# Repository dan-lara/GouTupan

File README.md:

# GouTupan

# User Guide —— GouTupan  

**Daniel, Vladislav, Xiaochen, Yulin**  

---

## Device Overview  

The system is an integrated environmental monitoring platform for agricultural greenhouses, based on an Arduino MKR WAN 1310 development board.  
Equipped with multiple specialized sensors, it enables real-time measurement of critical parameters for plant growth.  

Key features include:  
- Self-powered via solar panel with energy management circuit;  
- Waterproof design suitable for greenhouse environments with frequent irrigation;  
- Wireless data transmission via LoRaWAN;  
- Modular architecture for customized measurement points;  
- User interface: Web platform and local e-ink display for remote or on-site monitoring.  

---

## Installation and Usage Instructions  

The device transmits data using the LoRa protocol. Ensure the installation site has stable coverage from a LoRaWAN gateway.  
Without this, the following features will be unavailable: remote monitoring and historical data access.  

The system comprises four main modules:  
- **MCU Enclosure**: Contains the microcontroller and processing unit;  
- **"Mushroom" Sensor**: Measures ambient conditions;  
- **Soil Temperature & Humidity Sensor Array**;  
- **Solar Panel**: Powers the system.  

### MCU Enclosure  
Integrates an MKR WAN 1310 board, power management circuit, light sensor, and e-ink display.  
**Installation**: Position in a non-floodable area with direct ambient light exposure.  

### "Mushroom" Sensor  
Combines temperature, humidity, and gas sensors. Deploy at target measurement points.  
**Caution**: Avoid watering from below to prevent water ingress.  

### Soil Sensors  
- **Compact Probe**: Surface measurement (10 cm depth);  
- **Long Cylindrical Probe**: 50 cm length for deep soil measurements.  

### Solar Panel  
**Installation**: Place in a sunlit, elevated location to avoid water accumulation.  

### Activation  
Toggle the **side switch** on the MCU enclosure. Data transmission occurs every **3 minutes** (preconfigured).  

---

## Network and HMI Information  

### TTN (The Things Network)  
- **Username**: Levovitch  
- **Password**: demo1234  
- **Application Name**: `goutupan-mkr1310-vlad-xioa-dani-yuli`  
- **Device ID**: `goutupan-mkr1310-vlad-xioa-dani-yuli`  
- **AppEUI**: `AA2025AAAA2025AA`  
- **DevEUI**: `A8610A3234268310`  
- **AppKey**: `9qyh4jN6RBh4F@\$`  

### Useful Links  
- [Data Visualization Dashboard](https://goutupan.grafana.net/public-dashboards/d0bf3f14221d4401bc8c1fea2e30d045?var-device_var=goutupan-mkr1310-yulin-4&theme=light&from=now-7d&to=now&timezone=browser)  
- [Project GitHub Repository](https://github.com/dan-lara/GouTupan)  

---

## Sensor Specifications  

**Table 1: Technical Specifications of Environmental Sensors**  

| Module                     | Measured Parameters                                                                 | Technical Specifications                                                                 |
|----------------------------|-------------------------------------------------------------------------------------|------------------------------------------------------------------------------------------|
| **SCD30**                  | Carbon Dioxide (CO₂),<br>Temperature,<br>Humidity                                   | 400 ppm – 10,000 ppm (±30 ppm ±3%),<br>0–50 °C (±0.4 °C),<br>0–100% RH (±3% RH)         |
| **TCS34725/SI1145**        | Spectral Components (RGB/UV/IR)                                                    | λ = 465, 525, 615 nm,<br>Range: 400–1000 nm,<br>UV Detection: 280–400 nm (algorithmic)  |
| **SEN0605**                | Nitrogen (N), Phosphorus (P), Potassium (K)                                        | Range: 0–2999 mg/kg,<br>Resolution: 1 mg/kg,<br>Accuracy ≤5%,<br>IP68                   |
| **Grove Barometer 101020068** | Barometric Pressure                                                             | 30–110 kPa (±0.01 hPa)                                                                 |
| **SEN0322**                | Oxygen (O₂) Concentration                                                          | 0–25% vol (drift < 2%/month)                                                          |
| **SGP40**                  | Volatile Organic Compounds (VOC)                                                   | VOC Index: 0–500,<br>Ethanol: 0–1000 ppm                                              |
| **SHT30/SHT20**            | Temperature & Humidity                                                             | Humidity: 0–100% RH (±2%RH/±3%RH),<br>Temperature: -40–125 °C (±0.2 °C/±0.3 °C)       |
| **Grove Gas Sensor 101020820** | Ammonia (NH₃), <br>Carbon Monoxide (CO), <br>Nitrogen Dioxide (NO₂),<br>Propane (C₃H₈), <br>Butane (C₄H₁₀), <br>Methane (CH₄), <br>Hydrogen (H₂), <br>Ethanol (C₂H₅OH) | NH₃: 1–500 ppm,<br>CO: 5–5000 ppm,<br>NO₂: 0.05–2 ppm,<br>Hydrocarbons: 500–10,000 ppm,<br>H₂: 1–1000 ppm,<br>Ethanol: 1–500 ppm |

---

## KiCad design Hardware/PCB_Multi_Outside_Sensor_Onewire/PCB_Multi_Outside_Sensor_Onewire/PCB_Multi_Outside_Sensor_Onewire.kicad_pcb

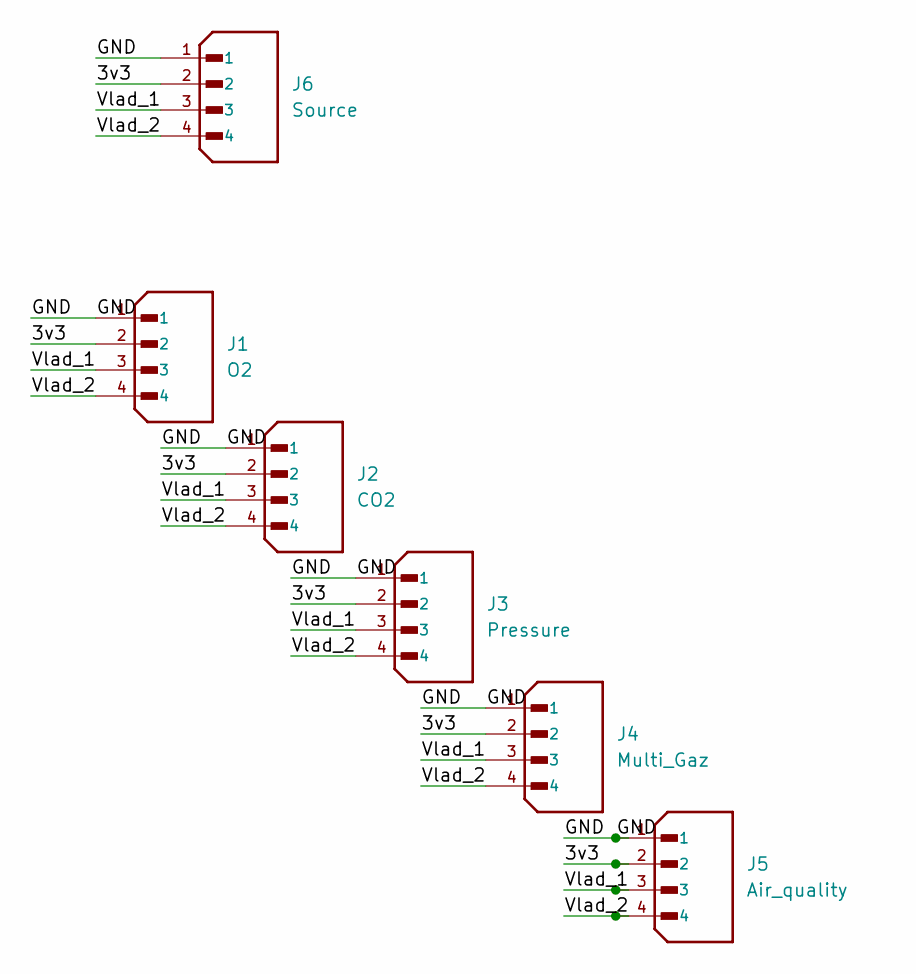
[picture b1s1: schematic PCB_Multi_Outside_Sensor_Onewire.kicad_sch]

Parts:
J1: O2; PinHeader_1x04_P2.00mm_Vertical; PARTREV 7/4/21
J2: CO2; PinHeader_1x04_P2.00mm_Vertical; PARTREV 7/4/21
J3: Pressure; PinHeader_1x04_P2.00mm_Vertical; PARTREV 7/4/21
J4: Multi_Gaz; PinHeader_1x04_P2.00mm_Vertical; PARTREV 7/4/21
J5: Air_quality; PinHeader_1x04_P2.00mm_Vertical; PARTREV 7/4/21
J6: Source; PinHeader_1x04_P2.00mm_Vertical; PARTREV 7/4/21

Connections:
/3v3: J1.2, J2.2, J3.2, J4.2, J5.2, J6.2
/GND: J1.1, J2.1, J3.1, J4.1, J5.1, J6.1
/Vlad_1: J1.3, J2.3, J3.3, J4.3, J5.3, J6.3
/Vlad_2: J1.4, J2.4, J3.4, J4.4, J5.4, J6.4

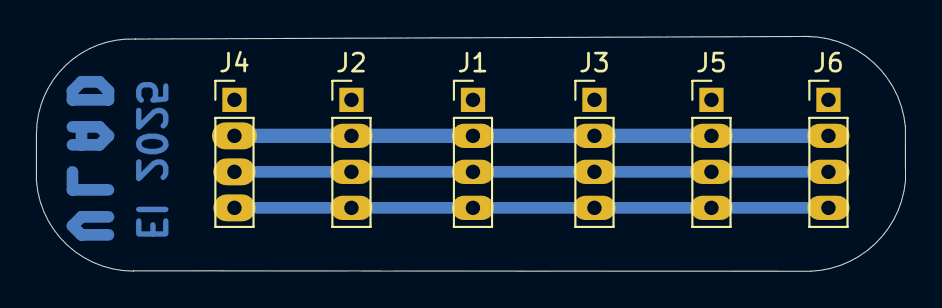
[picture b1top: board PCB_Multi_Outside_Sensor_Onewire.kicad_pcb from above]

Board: 2 copper layers, 48.3 x 13.0 mm, 6 parts (0 on the bottom side), 4 nets.

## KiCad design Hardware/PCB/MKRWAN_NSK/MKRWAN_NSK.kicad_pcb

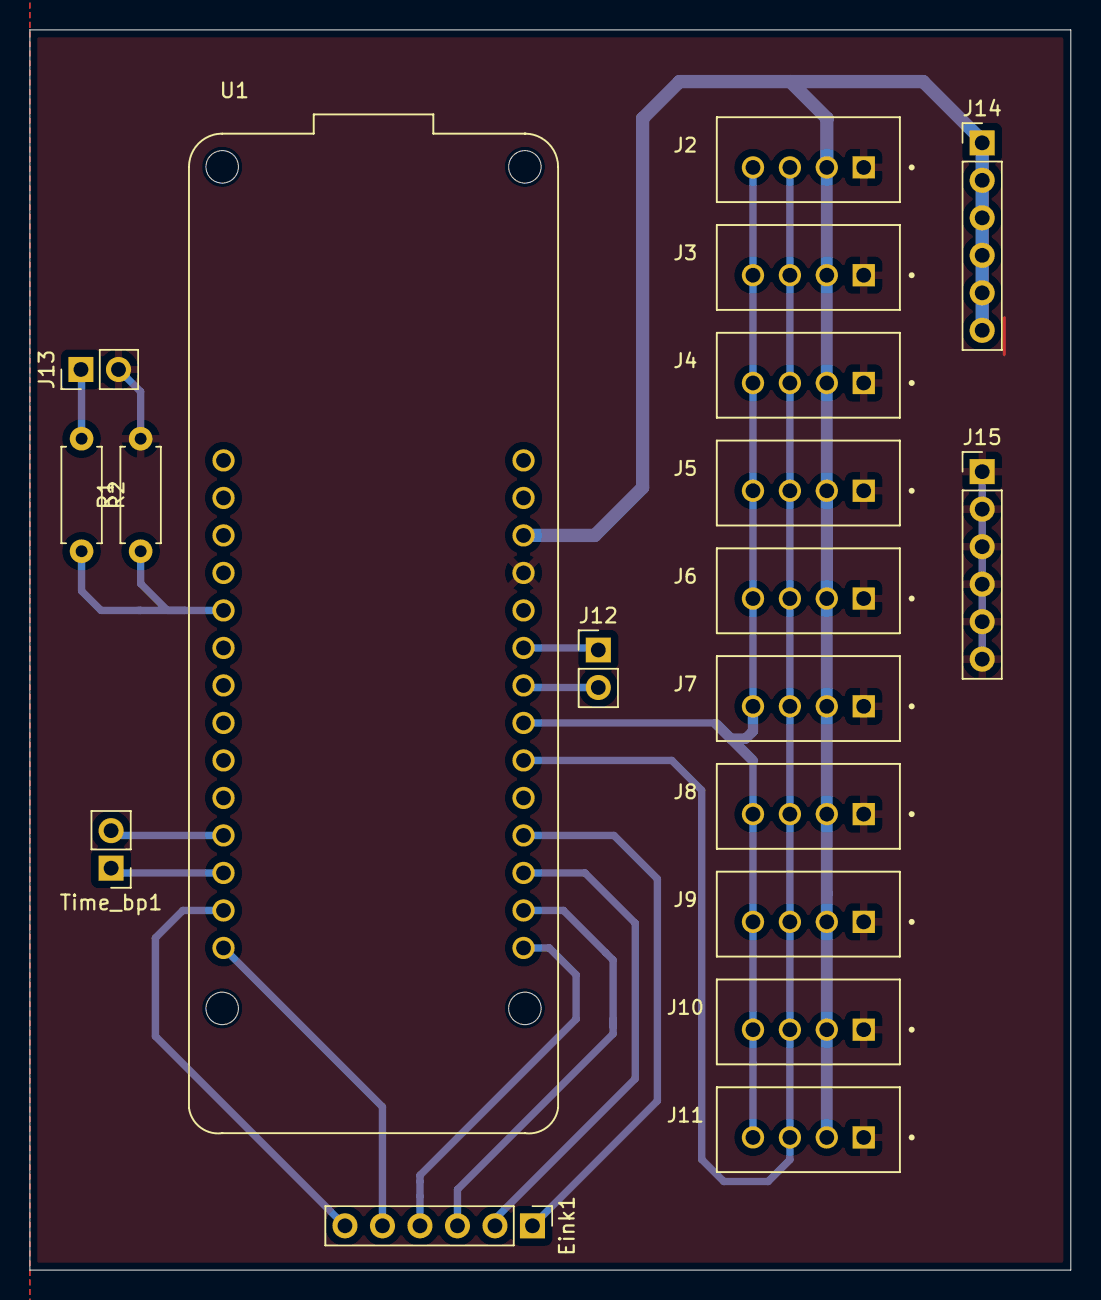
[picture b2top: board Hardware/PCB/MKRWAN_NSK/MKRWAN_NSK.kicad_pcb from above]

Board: 2 copper layers, 70.5 x 84.0 mm, 19 parts (0 on the bottom side), 16 nets.

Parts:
Eink1: Conn_01x06; PinHeader_1x06_P2.54mm_Vertical
J2: TH_Deep_Sensor; JST_B4B-XH-A_LF__SN_
J3: Other_Gaz_Sensor; JST_B4B-XH-A_LF__SN_
J4: UV_IR_Sensor; JST_B4B-XH-A_LF__SN_
J5: Extra_2; JST_B4B-XH-A_LF__SN_
J6: RGB_Sensor; JST_B4B-XH-A_LF__SN_
J7: CO2_Sensor; JST_B4B-XH-A_LF__SN_
J8: Pressure_Sensor; JST_B4B-XH-A_LF__SN_
J9: TH_Surface_Sensor; JST_B4B-XH-A_LF__SN_
J10: O2_Sensor; JST_B4B-XH-A_LF__SN_
J11: Extra_1; JST_B4B-XH-A_LF__SN_
J12: TTL; PinHeader_1x02_P2.54mm_Vertical
J13: Pont_diviseur; PinHeader_1x02_P2.54mm_Vertical
J14, J15: Conn_01x06; PinHeader_1x06_P2.54mm_Vertical
R1, R2: R_US; R_Axial_DIN0207_L6.3mm_D2.5mm_P7.62mm_Horizontal
Time_bp1: Conn_01x02; PinHeader_1x02_P2.54mm_Vertical
U1: ARDUINO_MKR_WAN_1310; BOARD_ARDUINO_MKR_WAN_1310

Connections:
/3v3: J2.2, J3.2, J4.2, J5.2, J6.2, J7.2, J8.2, J9.2, J10.2, J11.2, J14.1, J14.2, J14.3, J14.4, J14.5, J14.6, U1.J5_12 (+3V3)
/A3: R1.1, R2.2, U1.J3_5 (PA04/D18(PWM)/AIN(4)/A3)
/D2: Time_bp1.2, U1.J3_11 (PA10/D2(PWM))
/D3: Time_bp1.1, U1.J3_12 (PA11/D3(PWM))
/D4: Eink1.6, U1.J3_13 (PB10/D4(PWM))
/D5: Eink1.5, U1.J3_14 (PB11/D5(PWM))
/D6: Eink1.4, U1.J5_1 (PA20/D6(PWM))
/D7: Eink1.3, U1.J5_2 (PA21/D7(PWM))
/D8_MOSI: Eink1.2, U1.J5_3 (PA16/D8(PWM)/COPI(SC1))
/D9_SCK: Eink1.1, U1.J5_4 (PA17/D9/SCK(SC1))
/GND: J2.1, J3.1, J4.1, J5.1, J6.1, J7.1, J8.1, J9.1, J10.1, J11.1, J13.2, J15.1, J15.2, J15.3, J15.4, J15.5, J15.6, R1.2, U1.J5_11 (GND)
/RX_D13: J12.2, U1.J5_8 (PB23/D13/RX(SC5))
/SCL: J2.4, J3.4, J4.4, J5.4, J6.4, J7.4, J8.4, J9.4, J10.4, J11.4, U1.J5_7 (PA09/D12(PWM)/SCL(SC2))
/SDA: J2.3, J3.3, J4.3, J5.3, J6.3, J7.3, J8.3, J9.3, J10.3, J11.3, U1.J5_6 (PA08/D11/SDA(SC2))
/TX_D14: J12.1, U1.J5_9 (PB22/D14/TX(SC5))
unnamed: J13.1, R2.1

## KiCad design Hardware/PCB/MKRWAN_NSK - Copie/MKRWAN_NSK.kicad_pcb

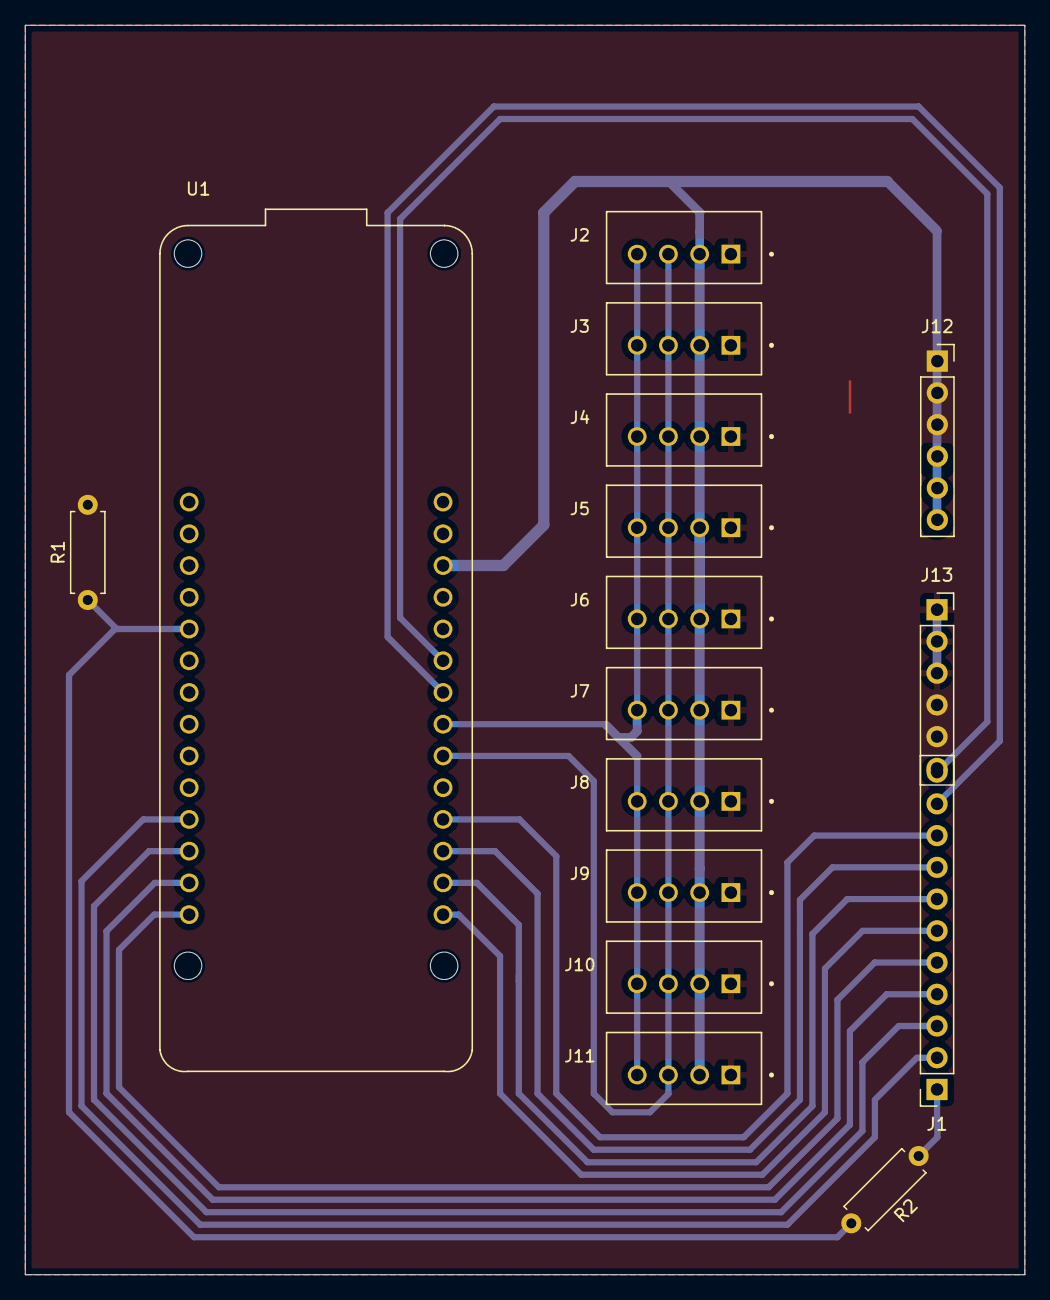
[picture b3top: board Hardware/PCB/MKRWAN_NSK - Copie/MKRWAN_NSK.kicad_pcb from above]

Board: 2 copper layers, 80.0 x 100.0 mm, 16 parts (0 on the bottom side), 16 nets.

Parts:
J1: Conn_01x11; PinSocket_1x11_P2.54mm_Vertical
J2: TH_Deep_Sensor; JST_B4B-XH-A_LF__SN_
J3: Other_Gaz_Sensor; JST_B4B-XH-A_LF__SN_
J4: UV_IR_Sensor; JST_B4B-XH-A_LF__SN_
J5: Extra_2; JST_B4B-XH-A_LF__SN_
J6: RGB_Sensor; JST_B4B-XH-A_LF__SN_
J7: CO2_Sensor; JST_B4B-XH-A_LF__SN_
J8: Pressure_Sensor; JST_B4B-XH-A_LF__SN_
J9: TH_Surface_Sensor; JST_B4B-XH-A_LF__SN_
J10: O2_Sensor; JST_B4B-XH-A_LF__SN_
J11: Extra_1; JST_B4B-XH-A_LF__SN_
J12: 3v3; PinSocket_1x06_P2.54mm_Vertical
J13: GND; PinSocket_1x06_P2.54mm_Vertical
R1, R2: R_US; R_Axial_DIN0207_L6.3mm_D2.5mm_P7.62mm_Horizontal
U1: ARDUINO_MKR_WAN_1310; BOARD_ARDUINO_MKR_WAN_1310

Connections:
/3v3: J2.2, J3.2, J4.2, J5.2, J6.2, J7.2, J8.2, J9.2, J10.2, J11.2, J12.1, J12.2, J12.3, U1.J5_12 (+3V3)
/A3: R1.1, R2.2, U1.J3_5 (PA04/D18(PWM)/AIN(4)/A3)
/D2: J1.2, U1.J3_11 (PA10/D2(PWM))
/D3: J1.3, U1.J3_12 (PA11/D3(PWM))
/D4: J1.4, U1.J3_13 (PB10/D4(PWM))
/D5: J1.5, U1.J3_14 (PB11/D5(PWM))
/D6: J1.6, U1.J5_1 (PA20/D6(PWM))
/D7: J1.7, U1.J5_2 (PA21/D7(PWM))
/D8_MOSI: J1.8, U1.J5_3 (PA16/D8(PWM)/COPI(SC1))
/D9_SCK: J1.9, U1.J5_4 (PA17/D9/SCK(SC1))
/GND: J2.1, J3.1, J4.1, J5.1, J6.1, J7.1, J8.1, J9.1, J10.1, J11.1, J13.1, J13.2, J13.3, R1.2
/RX_D13: J1.10, U1.J5_8 (PB23/D13/RX(SC5))
/SCL: J2.4, J3.4, J4.4, J5.4, J6.4, J7.4, J8.4, J9.4, J10.4, J11.4, U1.J5_7 (PA09/D12(PWM)/SCL(SC2))
/SDA: J2.3, J3.3, J4.3, J5.3, J6.3, J7.3, J8.3, J9.3, J10.3, J11.3, U1.J5_6 (PA08/D11/SDA(SC2))
/TX_D14: J1.11, U1.J5_9 (PB22/D14/TX(SC5))
unnamed: J1.1, R2.1

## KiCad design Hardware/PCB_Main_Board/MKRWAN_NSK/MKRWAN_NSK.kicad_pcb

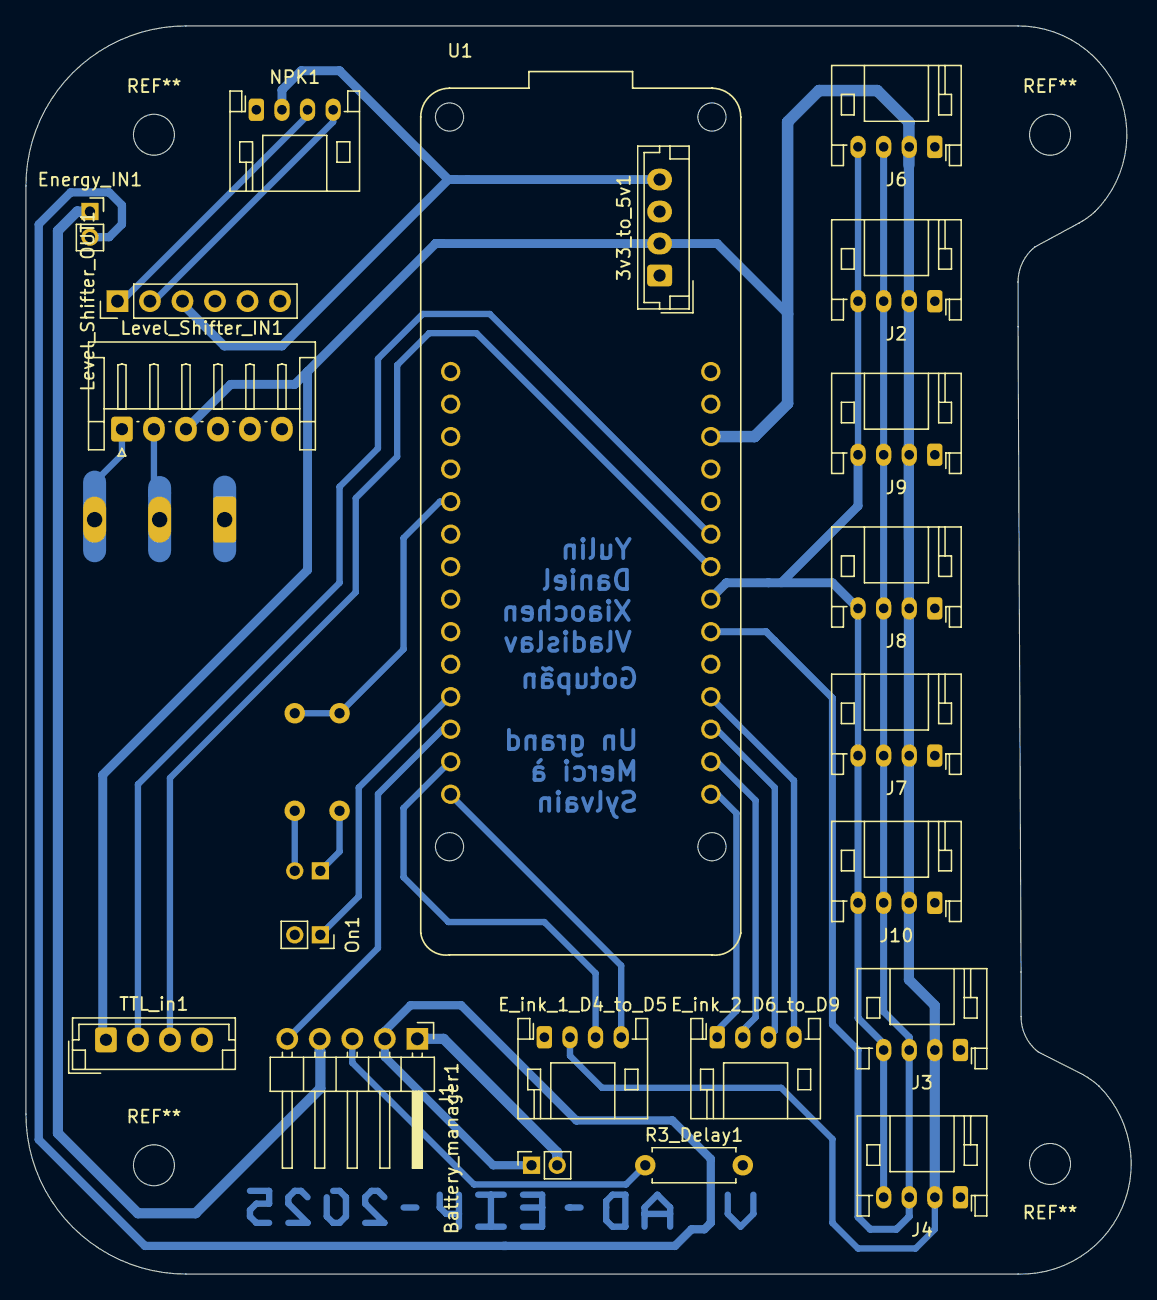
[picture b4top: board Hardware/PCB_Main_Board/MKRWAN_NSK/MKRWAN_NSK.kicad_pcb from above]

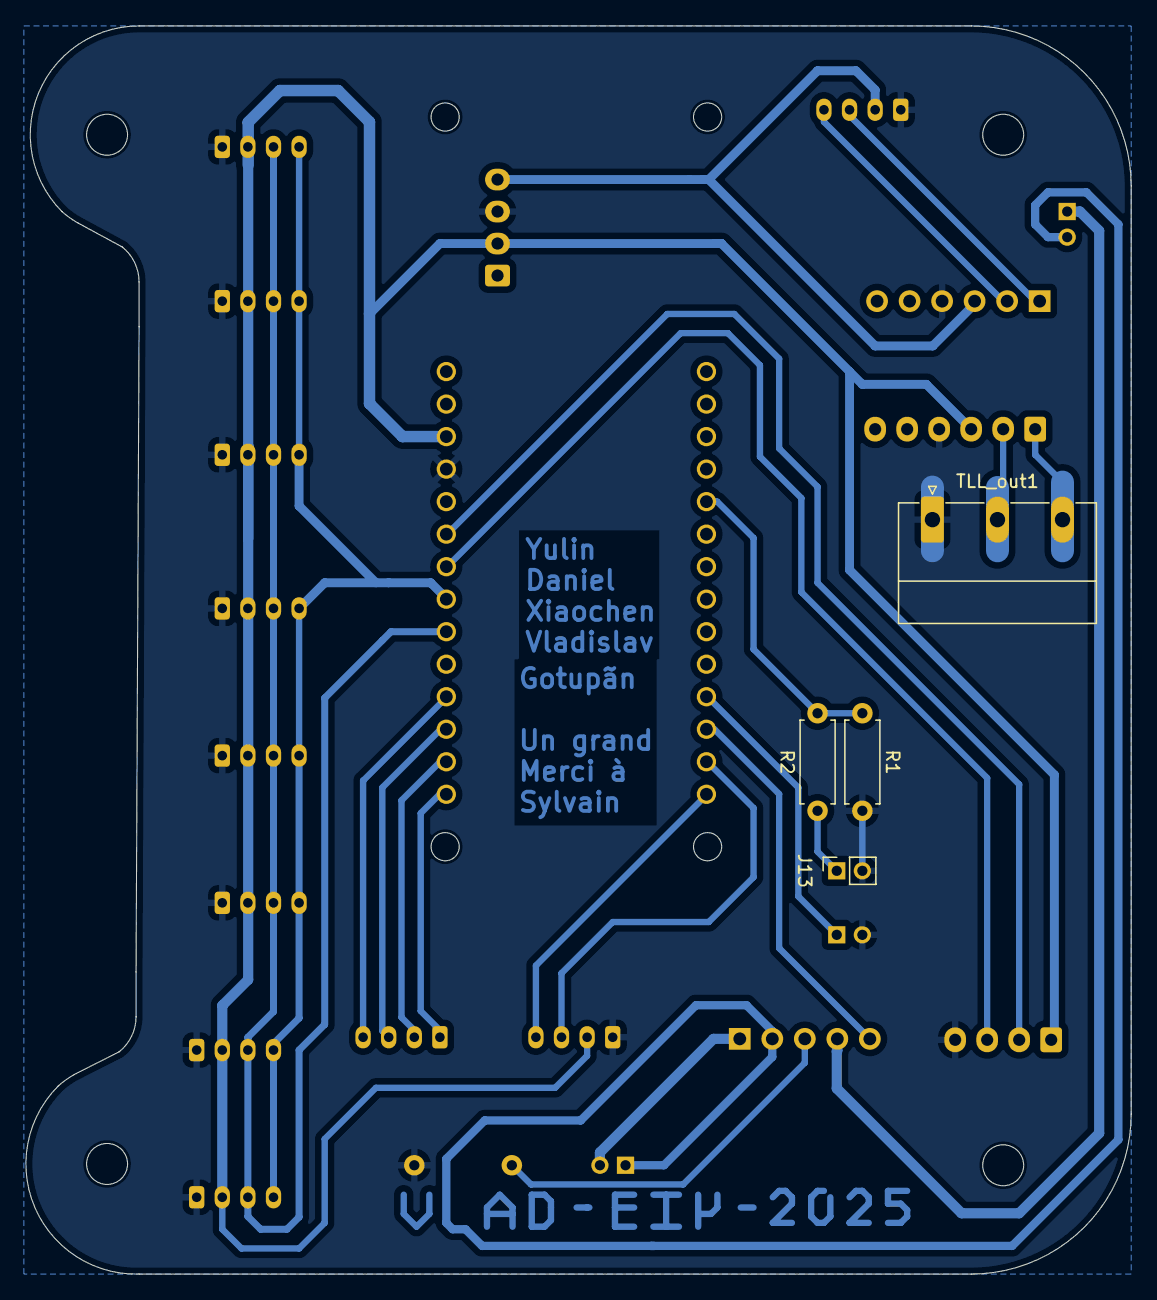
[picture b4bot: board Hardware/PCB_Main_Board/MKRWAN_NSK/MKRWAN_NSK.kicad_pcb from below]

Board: 2 copper layers, 86.3 x 97.5 mm, 25 parts (4 on the bottom side), 25 nets.

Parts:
3v3_to_5v1: Conn_01x04; JST_EH_B4B-EH-A_1x04_P2.50mm_Vertical
Battery_manager1: PinSocket_1x02_P2.00mm_Vertical
E_ink_1_D4_to_D5, E_ink_2_D6_to_D9: S4B-PH-K-S_LF__SN_; JST_PH_S4B-PH-K_1x04_P2.00mm_Horizontal
Energy_IN1: Pont_diviseur; PinSocket_1x02_P2.00mm_Vertical
J1: Conn_01x05; PinHeader_1x05_P2.54mm_Horizontal
J2: TH_Deep_Sensor; JST_PH_S4B-PH-K_1x04_P2.00mm_Horizontal
J3: Other_Gaz_Sensor; JST_PH_S4B-PH-K_1x04_P2.00mm_Horizontal
J4: UV_IR_Sensor; JST_PH_S4B-PH-K_1x04_P2.00mm_Horizontal
J6: RGB_Sensor; JST_PH_S4B-PH-K_1x04_P2.00mm_Horizontal
J7: CO2_Sensor; JST_PH_S4B-PH-K_1x04_P2.00mm_Horizontal
J8: Pressure_Sensor; JST_PH_S4B-PH-K_1x04_P2.00mm_Horizontal
J9: TH_Surface_Sensor; JST_PH_S4B-PH-K_1x04_P2.00mm_Horizontal
J10: O2_Sensor; JST_PH_S4B-PH-K_1x04_P2.00mm_Horizontal
J13: Pont_diviseur; PinSocket_1x02_P2.00mm_Vertical
Level_Shifter_IN1: Conn_01x06; JST_EH_S6B-EH_1x06_P2.50mm_Horizontal
Level_Shifter_OUT1: Conn_01x06; PinHeader_1x06_P2.54mm_Vertical
NPK1: S4B-PH-K-S_LF__SN_; JST_PH_S4B-PH-K_1x04_P2.00mm_Horizontal
On1: Off; PinSocket_1x02_P2.00mm_Vertical
R1, R2, R3_Delay1: R_US; R_Axial_DIN0207_L6.3mm_D2.5mm_P7.62mm_Horizontal
TLL_out1: Conn_01x03; PhoenixContact_MC_1,5_3-G-5.08_1x03_P5.08mm_Horizontal
TTL_in1: Conn_01x04; JST_EH_B4B-EH-A_1x04_P2.50mm_Vertical
U1: ARDUINO_MKR_WAN_1310; BOARD_ARDUINO_MKR_WAN_1310

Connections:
/3v3: 3v3_to_5v1.2, E_ink_1_D4_to_D5.2, J2.2, J3.2, J4.2, J6.2, J7.2, J8.2, J9.2, J10.2, Level_Shifter_IN1.3, TTL_in1.1, U1.J5_12 (+3V3)
/3v3_bis: Energy_IN1.1, J1.4
/5v: 3v3_to_5v1.4, Level_Shifter_OUT1.3, NPK1.2
/A3: R1.1, R2.2, U1.J3_5 (PA04/D18(PWM)/AIN(4)/A3)
/A_3v3: Level_Shifter_IN1.1, TLL_out1.3
/A_5v: Level_Shifter_OUT1.1, NPK1.3
/B_3v3: Level_Shifter_IN1.2, TLL_out1.2
/B_5v: Level_Shifter_OUT1.2, NPK1.4
/D2: On1.1, U1.J3_11 (PA10/D2(PWM))
/D3: J1.5, U1.J3_12 (PA11/D3(PWM))
/D4: E_ink_1_D4_to_D5.3, U1.J3_13 (PB10/D4(PWM))
/D5: E_ink_1_D4_to_D5.4, U1.J3_14 (PB11/D5(PWM))
/D6: E_ink_2_D6_to_D9.1, U1.J5_1 (PA20/D6(PWM))
/D7: E_ink_2_D6_to_D9.2, U1.J5_2 (PA21/D7(PWM))
/D8_MOSI: E_ink_2_D6_to_D9.3, U1.J5_3 (PA16/D8(PWM)/COPI(SC1))
/D9_SCK: E_ink_2_D6_to_D9.4, U1.J5_4 (PA17/D9/SCK(SC1))
/GND: 3v3_to_5v1.3, E_ink_1_D4_to_D5.1, J2.1, J3.1, J4.1, J6.1, J7.1, J8.1, J9.1, J10.1, J13.2, Level_Shifter_IN1.4, Level_Shifter_OUT1.4, NPK1.1, On1.2, R1.2, R3_Delay1.2, TLL_out1.1, TTL_in1.4, U1.J5_11 (GND)
/GND_bis: Battery_manager1.1, Energy_IN1.2, J1.2
/RX_D13: TTL_in1.3, U1.J5_8 (PB23/D13/RX(SC5))
/SCL: J2.4, J3.4, J4.4, J6.4, J7.4, J8.4, J9.4, J10.4, U1.J5_7 (PA09/D12(PWM)/SCL(SC2))
/SDA: J2.3, J3.3, J4.3, J6.3, J7.3, J8.3, J9.3, J10.3, U1.J5_6 (PA08/D11/SDA(SC2))
/TX_D14: TTL_in1.2, U1.J5_9 (PB22/D14/TX(SC5))
unnamed: Battery_manager1.2, J1.1
unnamed: J1.3, R3_Delay1.1
unnamed: J13.1, R2.1

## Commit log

2025-01-29 Add test line to README.md
2025-01-29 Add French README and language badges to main README
2025-01-31 Add Readme.fr version
2025-01-31 Modify README
2025-01-31 Update Readme3
2025-02-09 Add .gitignore files to multiple directories to exclude .env files #9
2025-02-09 Update language badge in README files to reflect correct French translation
2025-02-12 Add issue templates for bug reports, feature requests, and documentation
2025-02-12 Update issue templates
2025-02-12 Comment out contact links in issue template configuration
2025-02-13 TEST carte fonctionnelle - Closes #28
2025-02-13 TEST firmware version - Closes #29
2025-02-13 LoRaWAN: Initial transmission test on TTN - Closes #30 Closes #31
2025-02-14 Udtape security into arduino code - Progress #42
2025-02-14 Security fix mask - Progress #42
2025-02-14 Security fix mask - Progress #32
2025-02-16 Create LICENSE
2025-02-16 Refactored LoRa transmission into modular structure
2025-02-16 Firmware transmission compression - first compression validated offline
2025-02-16 Firmware transmission compression - Offline mode simplified
2025-02-16 Add TSL_2561 configuration file
    This file is to configurate the sensor of Lux TSL-2561
2025-02-16 Add the configuration file for Adafruit_TCS34725
    Add the configuration file for the RGB sensor Adafruit_TCS34725
2025-02-17 Rename Adafruit_TCS34725.ino to Transmission_Smart_Farm/Adafruit_TCS34725.ino
2025-02-17 Firmware transmission compression - Online mode fixed
2025-02-17 Modifier les lieus pour les fichier de capture
2025-02-17 Firmware transmission compression - Online mode 51 bytes prepared + CO2 compression done
2025-02-17 Firmware transmission compression - TTN_payload decompression
2025-02-18 Firmware transmission compression + Software decompression - Resend undelivered messages + Humidity
2025-02-18 Firmware transmission compression + Software decompression - compression_HEX_2 + Battery Level
2025-02-18 Firmware transmission compression - Final compression completed (RGB not included + extensible) - closes #32
2025-02-18 Software decompression - Final decompression completed (RGB not included + extensible) - closes #33
2025-02-19 Firmware transmission compression + Software decompression - Final bug fix (RGB not included)
2025-02-22 Firmware transmission compression - Fix bugs + improve temperature & humidity accuracy + adapt Arduino_KEY for different MKR modules
2025-02-22 Firmware transmission compression - Store payload in Flash if message not sent
2025-02-24 The programmes of RGB light and CO2 #37
2025-02-25 Sensor - barometer code HP20x v1
2025-02-25 Firmware transmission compression + Software decompression - RGB + Pressure + IR + UV included
2025-02-25 GITBOOK-4: No subject
2025-02-26 GitBook: No commit message
2025-02-27 Add DFRobot SEN0308 Soil Moisture Sensor library and example #59
2025-02-27 Update the welcome page
2025-02-27 Firmware Merging Sensor - Pressure + Outside Sensor + RGB + Light v0
2025-02-27 Firmware Merging Sensor - Pressure + Outside Sensor + RGB + Light + Deep-Surface Humidity v1
2025-02-27 Add BatteryManager class for battery monitoring functionality #60
2025-02-27 Firmware Merging Sensor - Pressure + Outside Sensor + RGB + Light + Deep-Surface Humidity+ Voltage v1.1
2025-02-27 Refactor BatteryManager to improve voltage reading and add getter methods for voltage and percentage
2025-02-28 Update the E-ink screen program, the current version can display certain text #61
2025-02-28 Optimized the character display logic, now horizontal display and vertical line wrapping can be achieved. #61
2025-03-03 Update the file .h for better display the character.
2025-03-03 Update the file .h for better display the character #61
2025-03-06 Software decompression - Gaz sensors var Initialisation + delay update
2025-03-06 Hardware PCB - PCB v0-v1 + Yulin's circuit diagram
2025-03-06 Firmaware compression + Software decompression - Gaz sensors
2025-03-06 Hardware PCB - PCB v2 dispatched section for sensors
2025-03-08 Hardware PCB - PCB v4 TTL + Timer + Boster + Level Shifter
2025-03-10 Add SHT3x sensor integration for temperature and humidity readings
2025-03-10 Refactor SHT3x sensor integration to use a new SHT3xSensor class for improved readability and maintainability
2025-03-10 Improved text display and is trying to access external data
2025-03-10 Improved text display and is trying to access external data #61
2025-03-10 This .ino is been tested and been proved that it can do clear all the content on the screen. #61
2025-03-11 Add .venv to .gitignore and create example.env for Grafana Pipeline configuration
2025-03-11 Add requirements.txt and implement TTN to InfluxDB data persistence #65
2025-03-11 Add README.md and image for Grafana Pipeline setup instructions #66
2025-03-11 Add Timertest.ino file for timer functionality implementation
2025-03-11 Add SGP40 sensor integration for VOC index readings
2025-03-11 Firmaware Sensor - Air contamination + O2 + UV-IR
2025-03-11 Hardware PCB - PCB
2025-03-18 Update the code of E-ink #61
2025-03-18 Update the code and fix the bug for SHT3xSensor. And update the code for the UV_IR sensor #70
2025-03-18 Fix: Fix conflicts between Local and Github
2025-03-18 Update SHT3xSensor.cpp
    Update the Update SHT3xSensor.cpp with the newest version #70
2025-03-18 Update SHT3xSensor.hpp
    Update the Update SHT3xSensor.hpp with the newest version #70
2025-03-18 Backup du dossier Mecanical - Sauvegarde des fichiers FreeCAD
2025-03-18 Update Mecanical - v9 version update
2025-03-18 Git ignore
2025-03-18 Ignore the folder '.vscode' #61
2025-03-18 Supprimer le dossier '.vscode' #61
2025-03-18 Mecanical - v10 + 3D printer files 2 pieces
2025-03-21 Update MAIN.ino
    update a test_mode for the program #72
2025-03-21 Refactor MAIN.ino: Adjust sensor initialization, modify delays, and implement timer functionality
2025-03-21 Hardware PCB_Mushroom - PCB_Mushroom v1 I2C HomeMade Hub
2025-03-21 Hardware PCB - PCB v5 TTL fixed + Holes Alignment
2025-03-21 Optimized the display and busy logic of E-ink. Now E-ink will not always be in busy state. #61
2025-03-21 Improved busy deadlock logic and optimized character display effects #61
2025-03-21 Upgate the code logic of E-ink and added TEST_MODE for Serial.print output #61
2025-03-21 Optimized the TEST_MODE #61
2025-03-22 Git ignore PCB zip
2025-03-23 Further configured E-ink, fixed the bug in SHT3x, tested the coordination of E-ink with SHT3x real-time data, integrated E-ink into MAIN.ino and preliminarily removed the bug in the code, waiting for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
2025-03-24 Updated comments to make them easier to understand. #61
2025-03-24 Add SoilSensor class for reading nitrogen, phosphorus, and potassium values
2025-03-24 Rename SEN0332_O2.hpp to SEN0322_O2.hpp
    Fixed a sensor name error
2025-03-24 Rename SEN0332_O2.cpp to SEN0322_O2.cpp
    Fixed a sensor name error
2025-03-24 Update MAIN.ino
    Fixed the O2 sensor name error
2025-03-24 Fixed O_2 sensor name error from 'SEN0332' to 'SEN0322'
2025-03-24 Traduire les commentaires et les résultats dans afficher.py en français
2025-04-06 Added images used in Wiki
2025-04-06 Update photo for the 'mushroom'
2025-04-06 Fixed a name bug.
2025-04-06 Update a photo for the MCU.
2025-04-06 Update a image for the web.
2025-04-06 Optimisation de la logique d'attente de l'e-ink
2025-04-07 Update the version final.
